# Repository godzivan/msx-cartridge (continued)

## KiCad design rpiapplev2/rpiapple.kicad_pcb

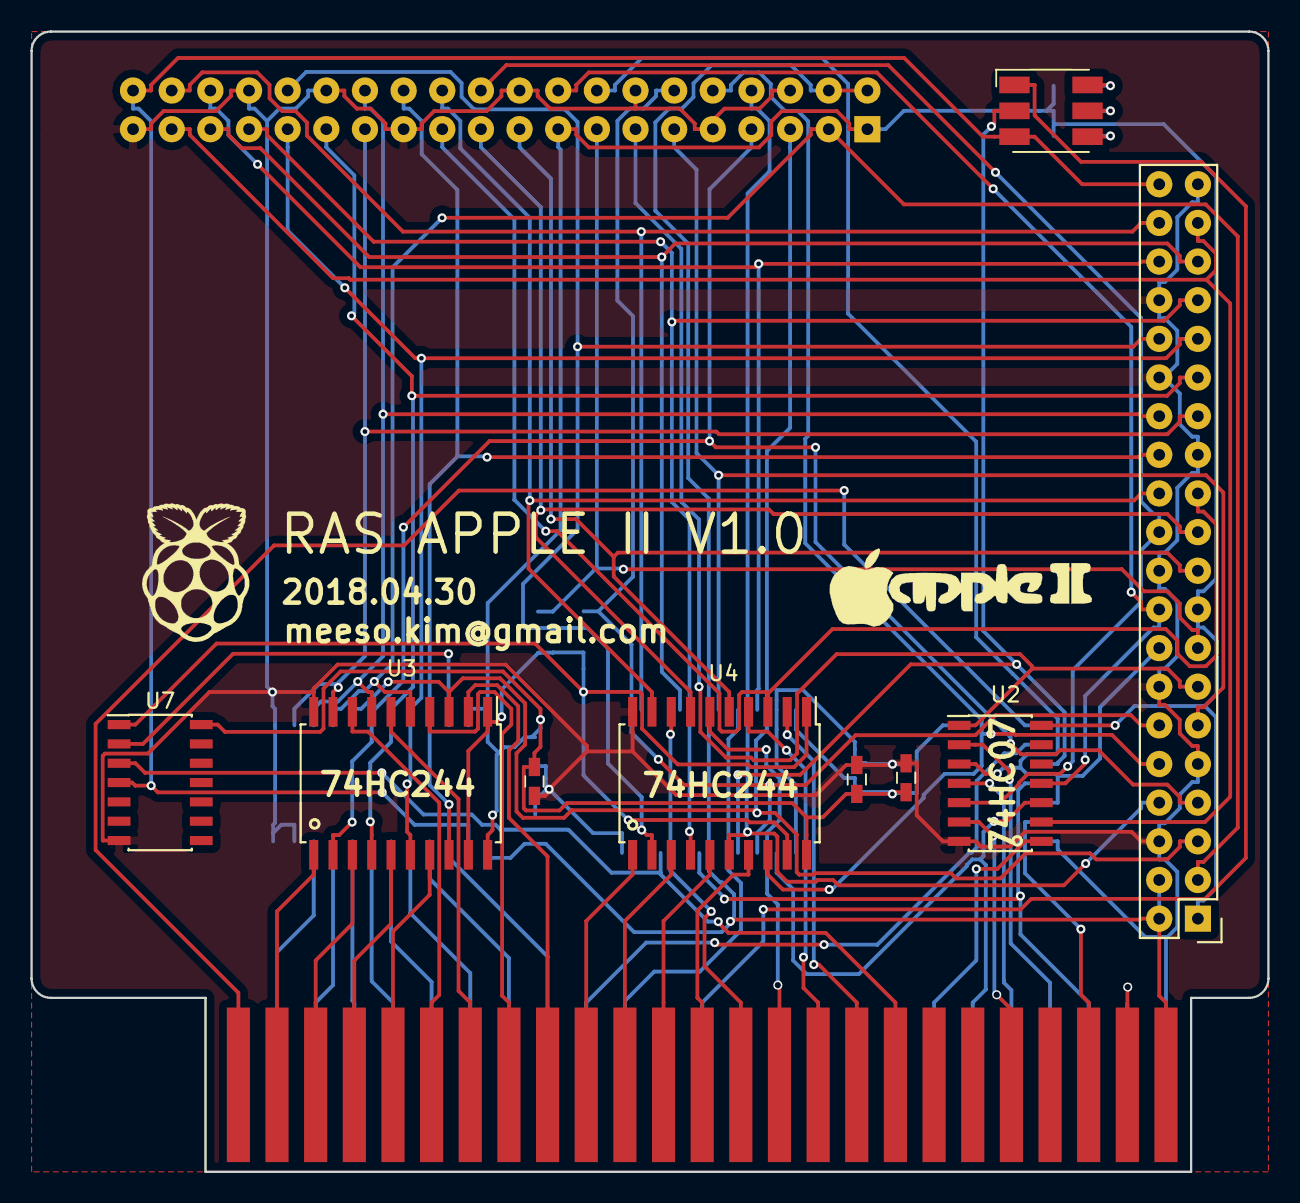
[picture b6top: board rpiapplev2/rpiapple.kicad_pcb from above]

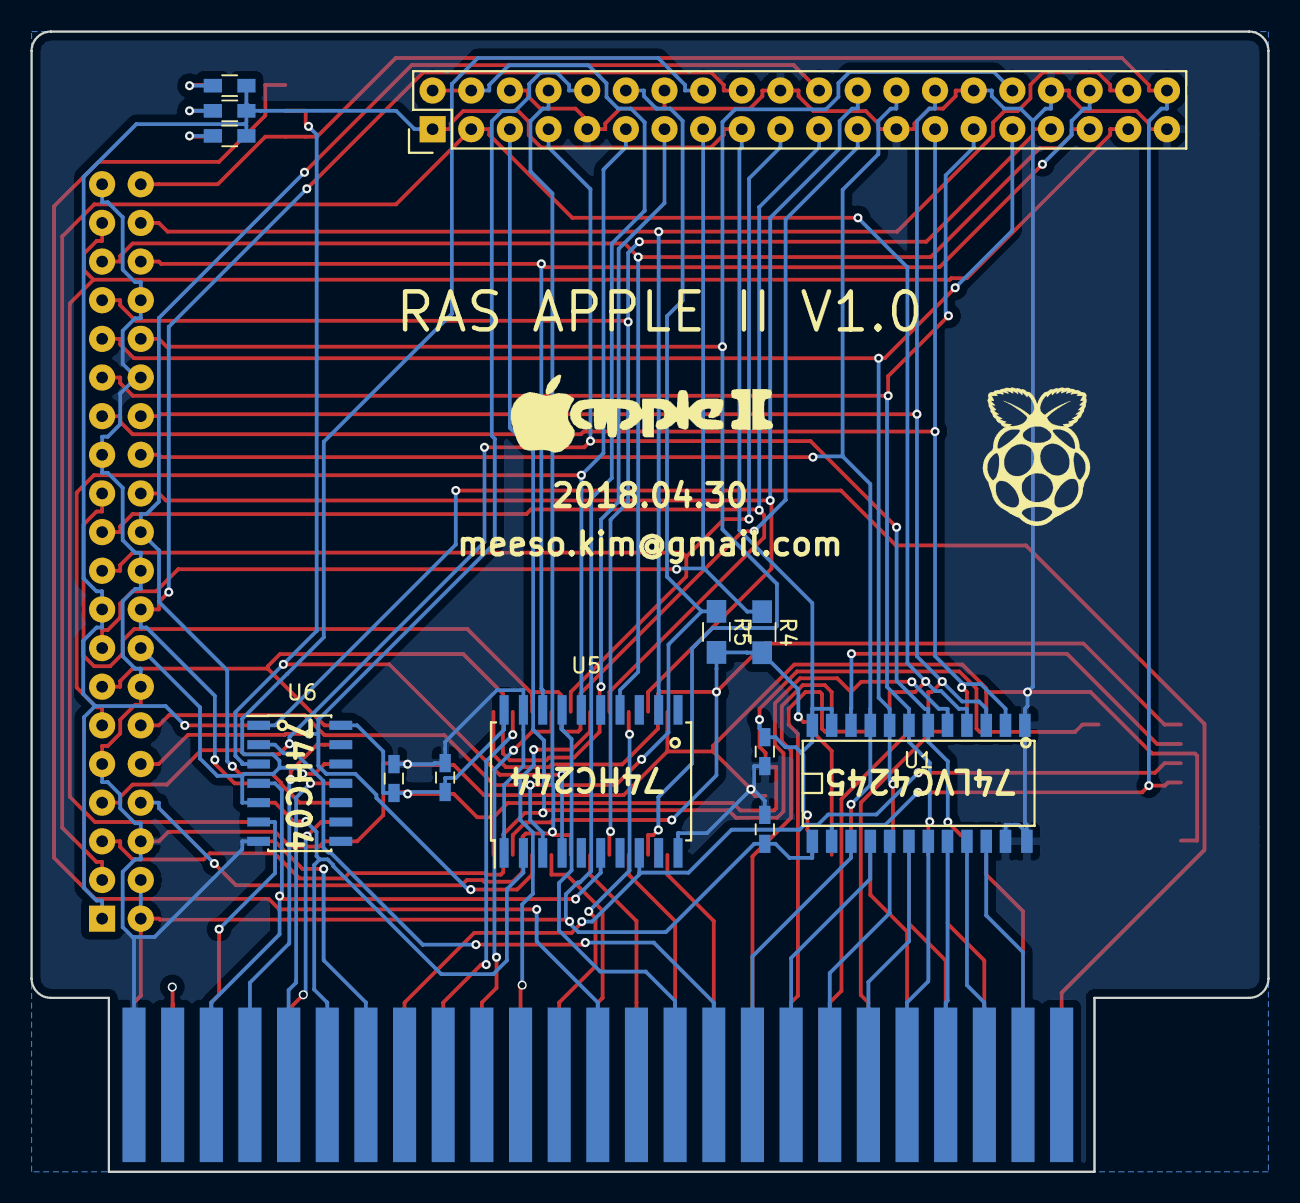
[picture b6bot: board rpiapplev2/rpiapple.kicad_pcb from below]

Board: 2 copper layers, 81.3 x 74.9 mm, 27 parts (15 on the bottom side), 74 nets.

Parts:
C1, C2, C3, C4, C5, C6, C7: C; C_0603_HandSoldering
D1: LED_RGB; LED_RGB_5050-6
G1, G4: LOGO; raspberry_pi_logo
G2, G3: LOGO; appleii_logo
J1, J2: Raspberry_Pi_2_3; Pin_Header_Straight_2x20
P1: A2Bus; Male_Card-Edge_50_pin__100_mil
R1, R2, R3: R; R_0603_HandSoldering
R4, R5: R; R_0805_HandSoldering
U1: LVC4245; SOIC-24
U2: 74LS05; SOIC-14_3.9x8.7mm_Pitch1.27mm
U3, U4, U5: 74HC244; SOIC-20W_7.5x12.8mm_Pitch1.27mm
U6: 74LS08; SOIC-14_3.9x8.7mm_Pitch1.27mm
U7: 74HC04; SOIC-14_3.9x8.7mm_Pitch1.27mm

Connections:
/5V0: C7.1, J1.2, J1.4, J2.2, J2.4, P1.25, U1.1
/A0: P1.2, U3.11
/A1: P1.3, U3.13
/A2: P1.4, U3.15
/A3: P1.5, U3.17
/A4: P1.6, U3.8
/A5: P1.7, U3.6
/A6: P1.8, U3.4
/A7: P1.9, U3.2
/A8: P1.10, U4.11
/A9: P1.11, U4.13
/A10: P1.12, U4.15
/A11: P1.13, U4.17
/A12: P1.14, U4.8
/A13: P1.15, U4.6
/A14: P1.16, U4.4
/A15: P1.17, U4.2
/ATN: R4.2, R5.2, U3.1, U3.19, U4.1, U4.19, U7.1
/D0: P1.49, U1.10
/D1: P1.48, U1.9
/D2: P1.47, U1.8
/D3: P1.46, U1.7
/D4: P1.45, U1.6
/D5: P1.44, U1.5
/D6: P1.43, U1.4
/D7: P1.42, U1.3
/DAT_DIR: D1.3, J1.40, J2.40, U1.2, U7.4
/DEVSEL: P1.41, U6.2
/DMAI: P1.24, P1.27
/INH: P1.32, U2.8
/INT0: P1.23, U6.6
/INTI: P1.28, U5.6, U6.4
/IOSEL: P1.1, U6.1
/IRQ: P1.30, U2.4
/NMI: P1.29, U2.2
/PH0: P1.40, U5.17
/PH1: D1.1, P1.38
/RA8: J1.24, J2.24, U4.9
/RA9: J1.21, J2.21, U4.7
/RA10: J1.19, J2.19, U4.5
/RA11: J1.23, J2.23, U4.3
/RA12: J1.32, J2.32, U4.12
/RA13: J1.33, J2.33, U4.14
/RA14: J1.8, J2.8, U4.16
/RA15: J1.10, J2.10, U4.18
/RC16: J1.36, J2.36, U5.18
/RC17: J1.11, J2.11, U5.16
/RC18: J1.12, J2.12, R5.1, U5.3
/RC19: J1.35, J2.35, U5.14
/RC20: J1.38, J2.38, U5.12
/RC22: J1.15, J2.15, R4.1
/RC23: J1.16, J2.16, U2.3, U6.5
/RC24: J1.18, J2.18, U2.11
/RC25: J1.22, J2.22, U2.5
/RC26: J1.37, J2.37, U2.9
/RC27: J1.13, J2.13, U2.1
/RD0: J1.27, J2.27, U1.14, U3.9
/RD1: J1.28, J2.28, U1.15, U3.7
/RD2: J1.3, J2.3, U1.16, U3.5
/RD3: J1.5, J2.5, U1.17, U3.3
/RD4: J1.7, J2.7, U1.18, U3.12
/RD5: J1.29, J2.29, U1.19, U3.14
/RD6: J1.31, J2.31, U1.20, U3.16
/RD7: J1.26, J2.26, U1.21, U3.18
/RDY: P1.21, U2.6
/RES: P1.31, U2.10, U5.2
/RW: P1.18, U5.8, U7.3
/SLTSL: D1.2, U5.4, U6.3
/nATN: U1.22, U7.2
GND: C1.2, C2.2, C3.2, C4.2, C5.2, C6.2, C7.2, J1.6, J1.9, J1.14, J1.20, J1.25, J1.30, J1.34, J1.39, J2.6, J2.9, J2.14, J2.20, J2.25, J2.30, J2.34, J2.39, P1.26, U1.11, U1.12, U1.13, U2.7, U3.10, U4.10, U5.1, U5.10, U5.19, U6.7, U7.7
unnamed: D1.4, R3.2
unnamed: D1.5, R2.2
unnamed: D1.6, R1.2
VCC: C1.1, C2.1, C3.1, C4.1, C5.1, C6.1, J1.1, J1.17, J2.1, J2.17, R1.1, R2.1, R3.1, U1.23, U1.24, U2.14, U3.20, U4.20, U5.20, U6.14, U7.14
